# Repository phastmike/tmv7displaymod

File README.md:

# Kenwood TM-V7 Display Mod

This repository contains a PCB design for a solution, to the "failing LCD display problem", by [OE9MKV](https://www.kinzi.net/node/16).
The implementation is based on reverse engineering some parts of the proprietary serial protocol from Kenwood.

The project uses KiCad 7 and the exported outputs are on the exports folder.

Includes schematic and PCB but you should refer to [OE9MKV](https://www.kinzi.net/node/16) and [PD2RLD](http://pd2rld.nl/) webpages for more
details, schematic, firmware, code and so on.

Thanks to both and in particular to [OE9MKV](https://www.kinzi.net/node/16) for all the effort in the development an implementation of a solution.

## Generated outputs

- [Check the Exports folder](exports/)

## Links

- [OE9MKV Webpage](https://www.kinzi.net/node/16)
- [PD2RLD Webpage](http://pd2rld.nl/)

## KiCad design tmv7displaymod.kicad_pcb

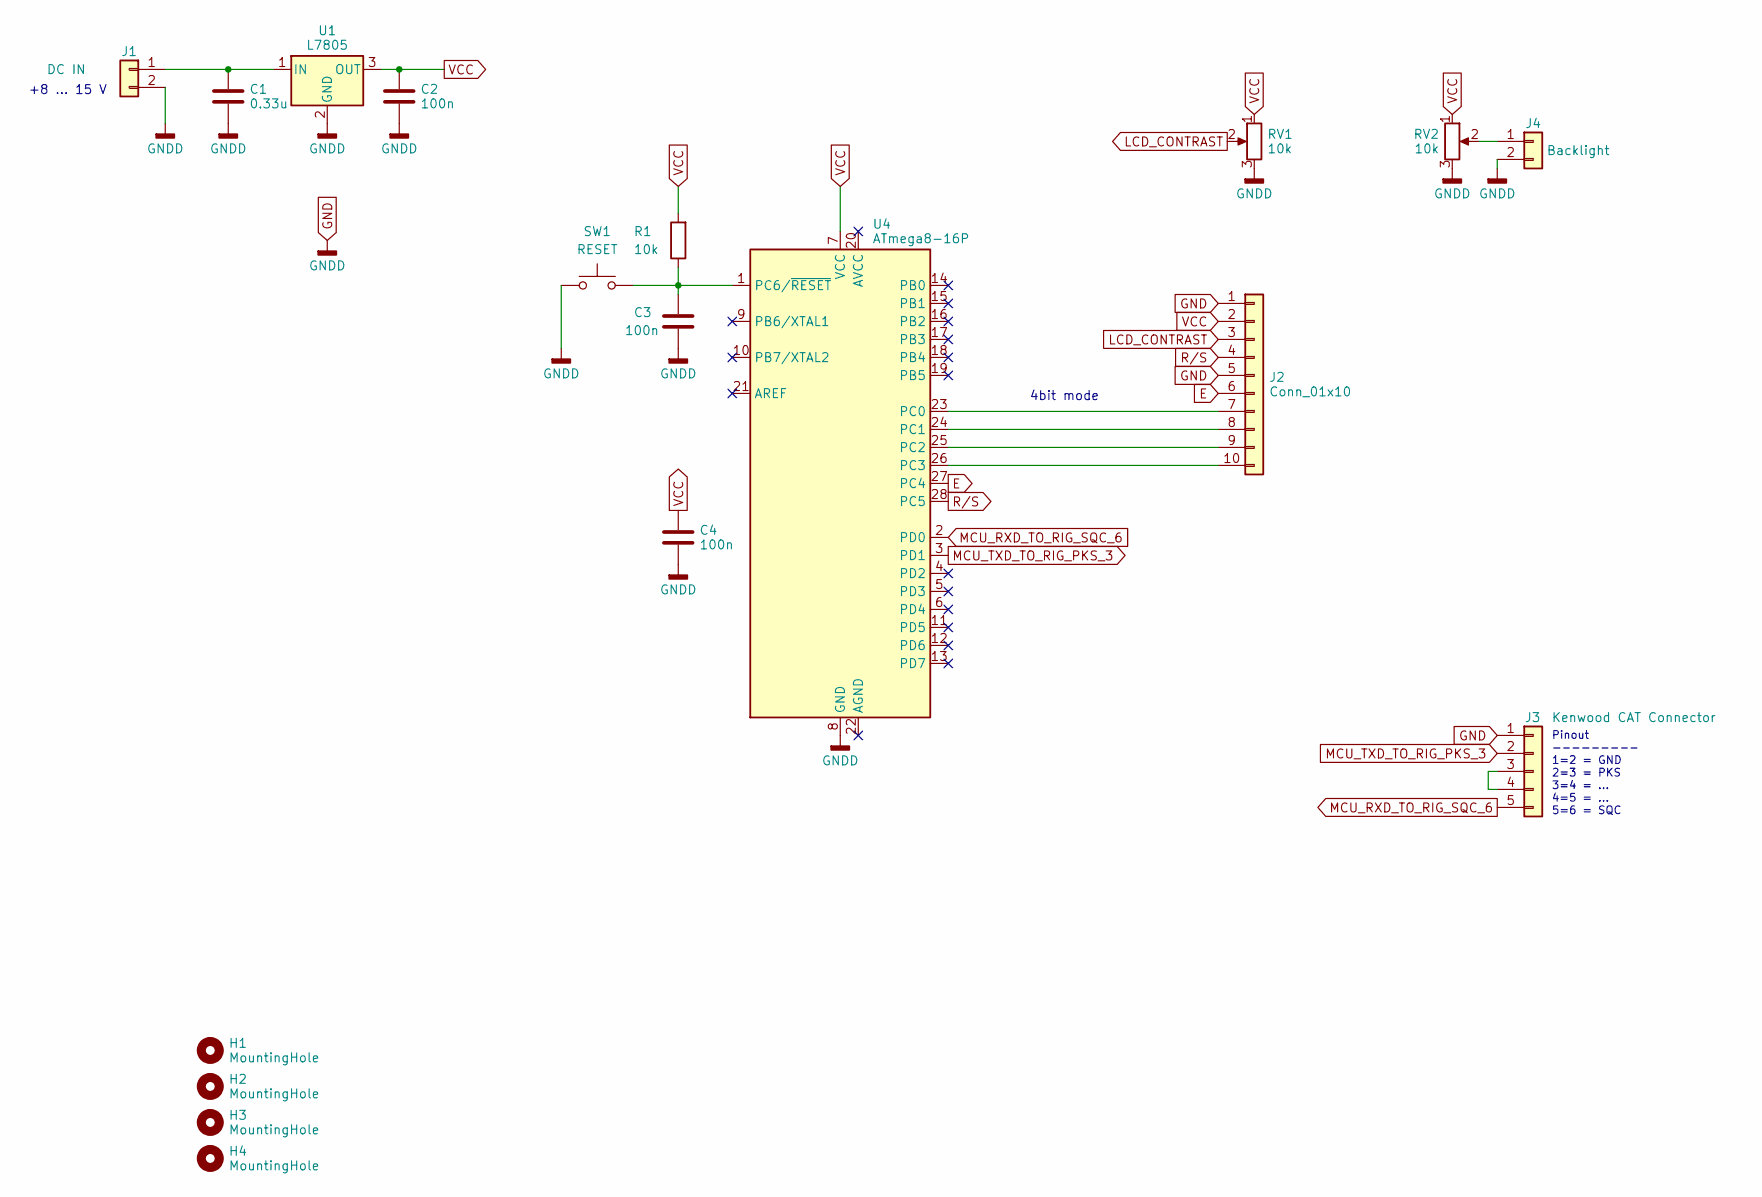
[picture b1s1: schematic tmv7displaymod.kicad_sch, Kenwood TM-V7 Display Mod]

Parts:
C1: 0.33u; C_Disc_D7.5mm_W5.0mm_P5.00mm
C2, C3, C4: 100n; C_Disc_D3.8mm_W2.6mm_P2.50mm
H1, H2, H3, H4: MountingHole; MountingHole_2.2mm_M2_Pad_Via
J1: DC IN; Molex_KK-254_AE-6410-02A_1x02_P2.54mm_Vertical
J2: Conn_01x10; Molex_KK-254_AE-6410-10A_1x10_P2.54mm_Vertical
J3: Kenwood CAT Connector; Molex_KK-254_AE-6410-05A_1x05_P2.54mm_Vertical
J4: Backlight; Molex_KK-254_AE-6410-02A_1x02_P2.54mm_Vertical
R1: 10k; R_Axial_DIN0204_L3.6mm_D1.6mm_P5.08mm_Horizontal
RV1, RV2: 10k; Potentiometer_Bourns_3296W_Vertical
SW1: RESET; PinHeader_1x02_P2.54mm_Vertical
U1: L7805; TO-220-3_Horizontal_TabDown
U4: ATmega8-16P; DIP-28_W7.62mm

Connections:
E: J2.6, U4.27 (PC4)
GND: C1.2, C2.2, C3.2, C4.2, J1.2, J2.1, J2.5, J3.1, J4.2, RV1.3, RV2.3, SW1.1, U1.2 (GND), U4.8 (GND)
LCD_CONTRAST: J2.3, RV1.2
MCU_RXD_TO_RIG_SQC_6: J3.5, U4.2 (PD0)
MCU_TXD_TO_RIG_PKS_3: J3.2, U4.3 (PD1)
unnamed: C1.1, J1.1, U1.1 (IN)
unnamed: J2.7, U4.23 (PC0)
unnamed: J2.8, U4.24 (PC1)
unnamed: J2.9, U4.25 (PC2)
unnamed: J2.10, U4.26 (PC3)
unnamed: J3.3, J3.4
unnamed: J4.1, RV2.2
unnamed: C3.1, R1.1, SW1.2, U4.1 (PC6/~RESET)
R/S: J2.4, U4.28 (PC5)
VCC: C2.1, C4.1, J2.2, R1.2, RV1.1, RV2.1, U1.3 (OUT), U4.7 (VCC)

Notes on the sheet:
4bit mode
Pinout --------- 1=2 = GND 2=3 = PKS 3=4 = ... 4=5 = ... 5=6 = SQC
+8 ... 15 V

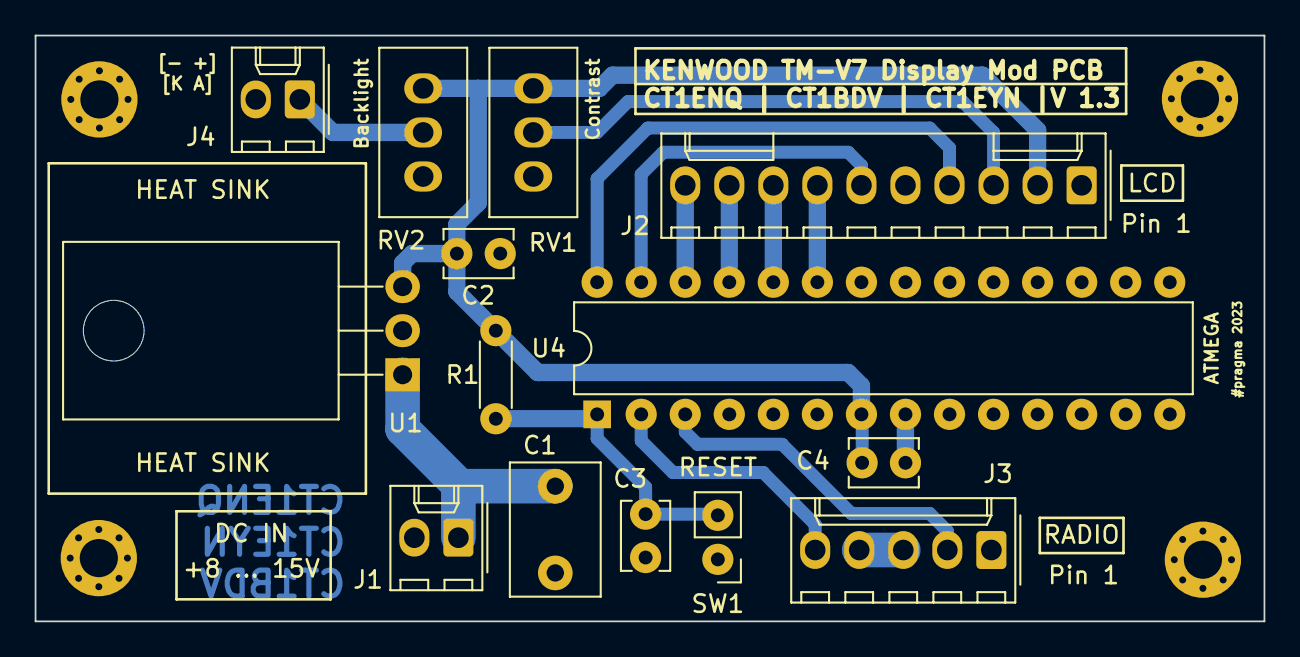
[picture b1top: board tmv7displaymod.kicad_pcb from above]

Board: 2 copper layers, 70.9 x 33.8 mm, 18 parts (0 on the bottom side), 15 nets.

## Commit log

2023-08-02 Typo fix
2023-08-02 minor tweaks
2023-08-03 Minor fixes and tweaks
2023-08-03 tweak
2023-08-07 minor tweaks. Brightness was in fact contrast
2023-08-14 Additional tweaks. xchanged rs for e and added backlight.
2023-08-22 V1.2 - minor tweaks and new exports. Organized exports
2023-08-22 Minor fixes, updated README
2023-09-10 Fixed missing callsigns in silkcreen layer
2023-09-10 Exported output for v1.3
2023-09-24 More tweaks to v1.3
